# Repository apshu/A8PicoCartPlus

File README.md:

# A8PicoCart+ (A8PicoCart with autoboot and OLED GFX)

The aim of the A8PicoCart+ is to add autoboot feature to the excellent A8PicoCart. 

The autoboot eliminates the need to navigate trough a complex filesystem or many files (e.g. when playing zaxxon :). On power up it checks if the onboard I²C EERAM stores a valid filename. If the filename is valid, it loads the file automatically before showing the selector interface. If the last file can't be loaded (e.g. deleted) the selector GUI is shown.

If the selector UI is needed, press the Choose button on the cart during powerup.

A simple I²C OLED display is included for fun. The 128×64 monochrome display shows the loaded cart logo if the cartridge is recognized as extended format.

A new PCB was needed for the + functionality. The new PCB is 100% compatible with the original firmware, while utilizing the originally unconnected GP28 & GP29 pins for I²C.

3D printable box with the + features is available.

# A8PicoCart (UnoCart on a Raspberry Pi Pico clone)

The A8PicoCart is a multi-cart for the Atari 8-bit (XL/XE) which you can make at home with only basic soldering skills.
It is based on my earlier UnoCart design but uses a very inexpensive Raspberry Pi Pico clone (£2-3) for an easy build.

When plugged into a PC by USB it becomes a Mass Storage device allowing ROM/CAR/XEX & ATR files to be copied to the cartridge.
When plugged into an Atari these files are shown on the menu and the device will either emulate the selected cartridge type or
act as a XEX file launcher. It also has (very) limited support for ATR files allowing you to do some programming and save your
work to an ATR file.

This page contains everything you need to build the project - firmware to flash to your purple Pico clone, Kicad PCB design files to make a PCB and 3d print files for a nice case. The source code for everything is also here. There is also a manual detailing the full capabilities of the cartridge.

If you build an A8PicoCart consider donating to help fund this and my future projects:

## Quick Start

Get yourself a purple Raspberry Pi Pico clone (see [this thread](https://forums.raspberrypi.com/viewtopic.php?t=337976) for details) and order a PCB using the KiCad board files provided. You have a choice of two PCB designs - the XE design is for use uncased, with the Pico on the top surface. The XL/XE version is desgined to be mounted in a case (though can be used uncased too) with the Pico on the bottom/back surface. Once you have the Pico clone and PCB, solder the pico as pictured below, depending on your PCB version. Program the firmware onto the device by pressing BOOTSEL on the board and connecting to USB on a PC and drag the firmware (UF2 file) onto the device. It should then remount as A8-PICOCART so you can copy Atari CAR & XEX files to it. Unmount, then plug into your Atari and play! Optionally solder a reset button to reset back to the menu.

**Note**: this project does not work with the official green RPi Pico board. Although the official board has the same
number of physical pins (and will therefore fit in the PCB) - the actual pin functions are different and attempting to use
it may damage the Pico and/or your Atari. The purple clones are cheaper and have a greater number of usuable GPIO pins - 
this is required for the cartridge port emulation to work.

**Warning**: always disconnect from PC/USB before plugging into your Atari or you will damage your Atari and/or PC. This warning mainly
applies to the XE/uncased version of the PCB. The newest version of the XL/XE board makes it physically impossible to connect USB when the
cartridge is inserted in an Atari.

## Inserting the cartridge

Depending on which PCB you choose the Pico clone may be mounted on the front or back of the PCB. When you insert
the cartridge in the Atari make sure the "S..A" side of the cartridge edge (NOT the "1..15" side) is facing upwards (XE) or towards you (XL).

## Purple Pico clones

The firmware is designed for the Purple Pico clones with USB C connector and 16Megs of flash and a single button (BOOTSEL).
I've received these devices with two different types of SPI flash chips - Winbond and (slower) Z-bit. The firmware has been tested with both types.

The project defines a custom board with a higher value for PICO_FLASH_SPI_CLKDIV so it supports the slower Z-bit flash.

Be aware that it's possible you might get one with another type of flash memory chip that has not been tested.

## Reset button

You can solder a push button to the cartridge to get back to the menu and avoid wear on your Atari power switch.
When you reset the cartridge the Atari will crash - just push reset on the Atari itself to get back to the menu.

The button used is a 6x6mm thru-hole tactile momentary switch. If you are going to print a case, then 9mm+ height is suitable.
When you solder the button to the PCB - make sure the lower two holes in the PCB are bridged only when the button is pressed.

It works simply by pulling the RUN pin on the pico clone to ground to reset.

## 3D print files

The STL files can be used to print a 3 part (front, back and logo) cartridge shell. The 2-tone logo is achieved by
changing the filament at the correct z-position when printing a8pico_logo.stl. You'll also need two M3 15mm screws.

## Changelog

* 7 Oct 2023 - Add new PCB & case design files to make it impossible to insert USB when plugged into Atari. Add support for Microcart (CAR type 52) cartridges. Updated manual.
* 29 Oct 2023 - Adds 3 new cartridge types (thanks to ascrnet)

## Credits

* Design, hardware and firmware by Robin Edwards (electrotrains at atariage)
* XEX loader and OS modifications by Jonathan Halliday (flashjazzcat at atariage)
* Altirra LLE OS used with permision from Avery Lee (phaeron at atariage)

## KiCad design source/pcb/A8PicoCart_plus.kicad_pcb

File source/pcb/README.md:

# XL/XE version PCB (which fits the 3d printed case design)

* KiCad Project wirh 3D models 
* KiCad Version: 8.0.3, release build
* A zip file of the gerbers (JLCPCB specification).
* Updated version with EERAM and OLED display 
 
## PCB specifications:
* 70.04 × 53.8 mm
* 2 layers
* 1.6 mm thickness
* Minimum drill 0.3 mm
* Hard gold fingers with bevelled edge will make your PCB last longer, but at a much higher cost.

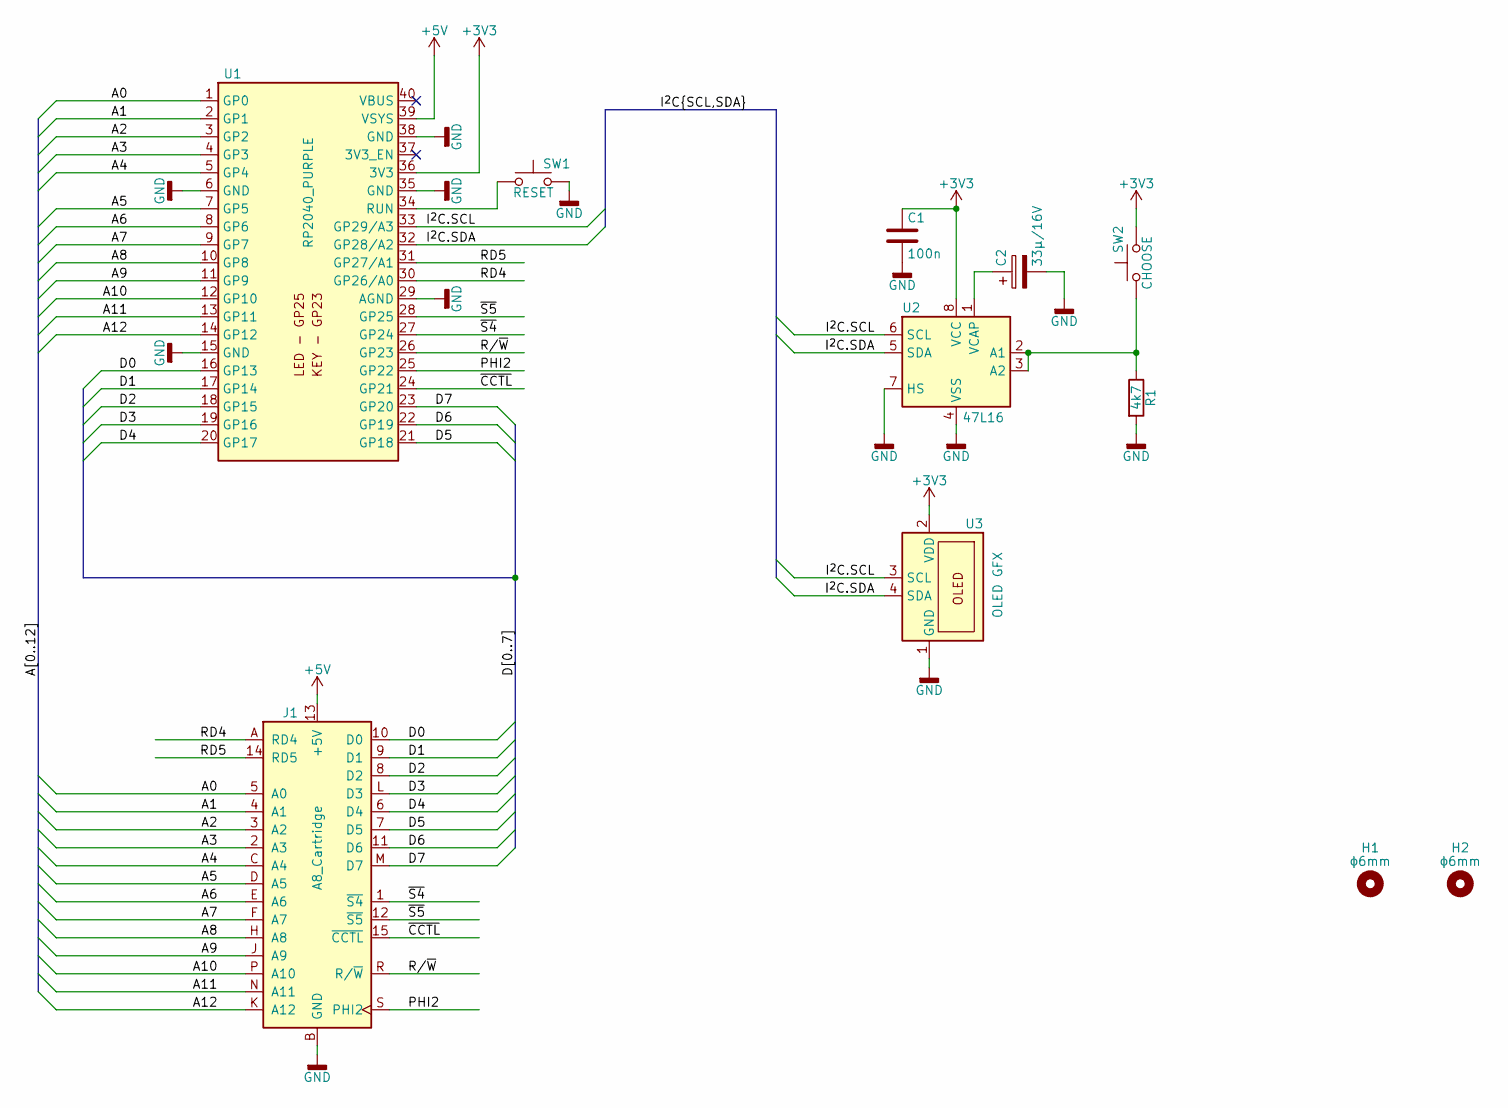
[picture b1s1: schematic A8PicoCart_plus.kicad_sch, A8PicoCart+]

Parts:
C1: 100n; C_0805_2012Metric_Pad1.18x1.45mm_HandSolder
C2: 33µ/16V; CP_Radial_D4.0mm_P2.00mm
H1, H2: ϕ6mm; MountingHole_6mm
J1: A8_Cartridge; Cartridge_A8
R1: 4k7; R_0805_2012Metric_Pad1.20x1.40mm_HandSolder
SW1: RESET; SW_PUSH_6mm_H8mm
SW2: CHOOSE; SW_PUSH_6mm_H8mm
U1: RP2040_PURPLE; RP2040_purple_nodbg
U2: 47L16; SOIC-8_3.9x4.9mm_P1.27mm
U3: OLED GFX; JST_XH_B4B-XH-A_1x04_P2.50mm_Vertical

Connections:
+3V3: C1.1, SW2.2, U1.36 (3V3), U2.8 (VCC), U3.2 (VDD)
+5V: J1.13 (+5V), U1.39 (VSYS)
/A0: J1.5 (A0), U1.1 (GP0)
/A1: J1.4 (A1), U1.2 (GP1)
/A2: J1.3 (A2), U1.3 (GP2)
/A3: J1.2 (A3), U1.4 (GP3)
/A4: J1.C (A4), U1.5 (GP4)
/A5: J1.D (A5), U1.7 (GP5)
/A6: J1.E (A6), U1.8 (GP6)
/A7: J1.F (A7), U1.9 (GP7)
/A8: J1.H (A8), U1.10 (GP8)
/A9: J1.J (A9), U1.11 (GP9)
/A10: J1.P (A10), U1.12 (GP10)
/A11: J1.N (A11), U1.13 (GP11)
/A12: J1.K (A12), U1.14 (GP12)
/D0: J1.10 (D0), U1.16 (GP13)
/D1: J1.9 (D1), U1.17 (GP14)
/D2: J1.8 (D2), U1.18 (GP15)
/D3: J1.L (D3), U1.19 (GP16)
/D4: J1.6 (D4), U1.20 (GP17)
/D5: J1.7 (D5), U1.21 (GP18)
/D6: J1.11 (D6), U1.22 (GP19)
/D7: J1.M (D7), U1.23 (GP20)
/I^{2}C.SCL: U1.33 (GP29/A3), U2.6 (SCL), U3.3 (SCL)
/I^{2}C.SDA: U1.32 (GP28/A2), U2.5 (SDA), U3.4 (SDA)
/PHI2: J1.S (PHI2), U1.25 (GP22)
/RD4: J1.A (RD4), U1.30 (GP26/A0)
/RD5: J1.14 (RD5), U1.31 (GP27/A1)
/R/~W: J1.R (R/~W), U1.26 (GP23)
/~CCTL: J1.15 (~CCTL), U1.24 (GP21)
/~S4: J1.1 (~S4), U1.27 (GP24)
/~S5: J1.12 (~S5), U1.28 (GP25)
GND: C1.2, C2.2, J1.B (GND), R1.2, SW1.2, U1.6 (GND), U1.15 (GND), U1.29 (AGND), U1.35 (GND), U1.38 (GND), U2.4 (VSS), U2.7 (HS), U3.1 (GND)
unnamed: SW1.1, U1.34 (RUN)
unnamed: R1.1, SW2.1, U2.2 (A1), U2.3 (A2)
unnamed: C2.1, U2.1 (VCAP)

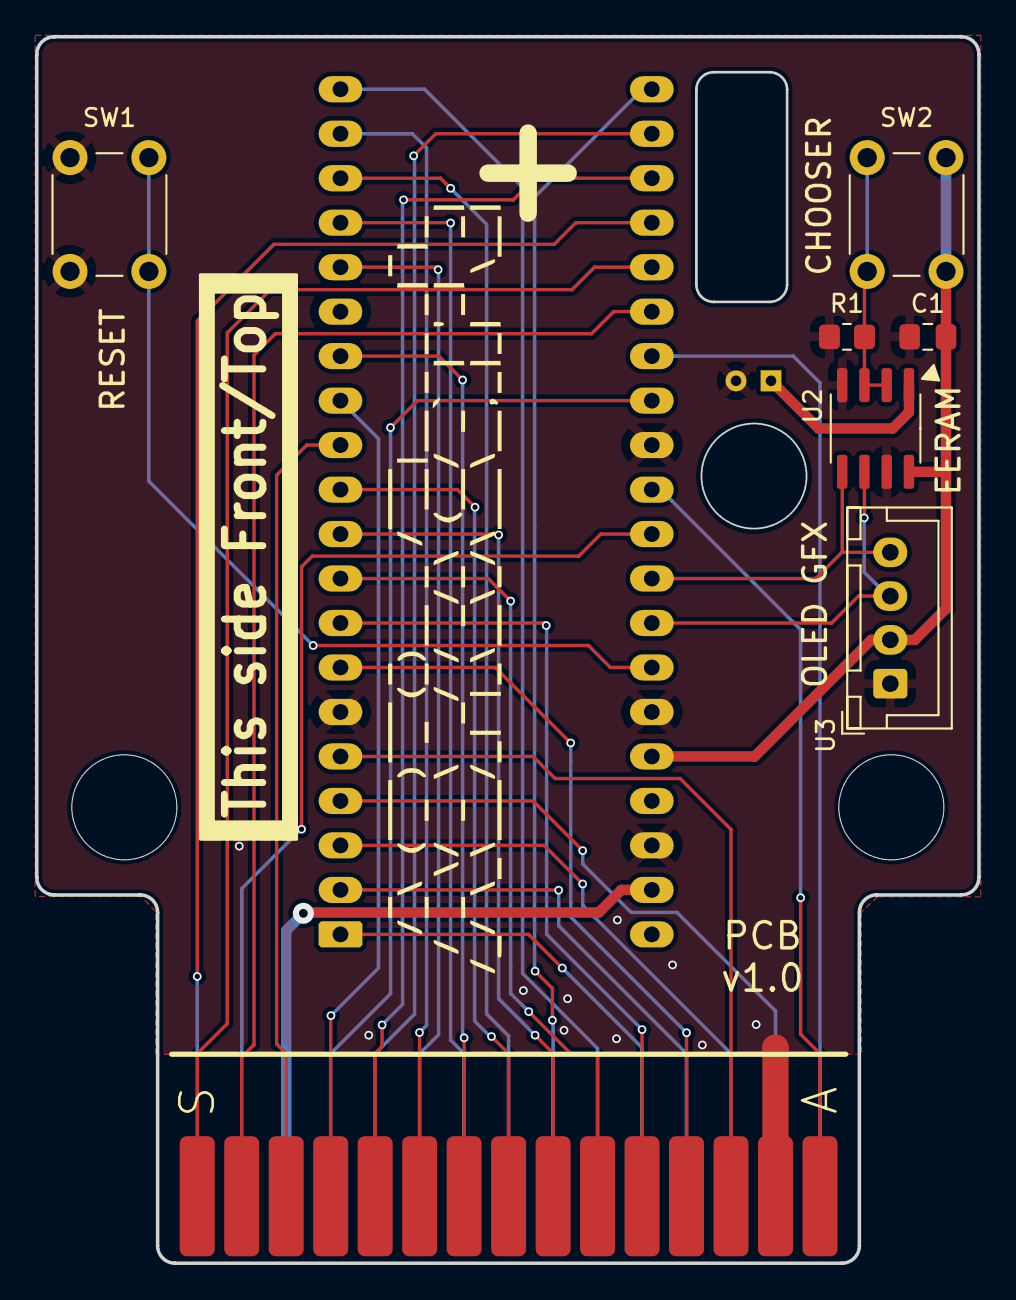
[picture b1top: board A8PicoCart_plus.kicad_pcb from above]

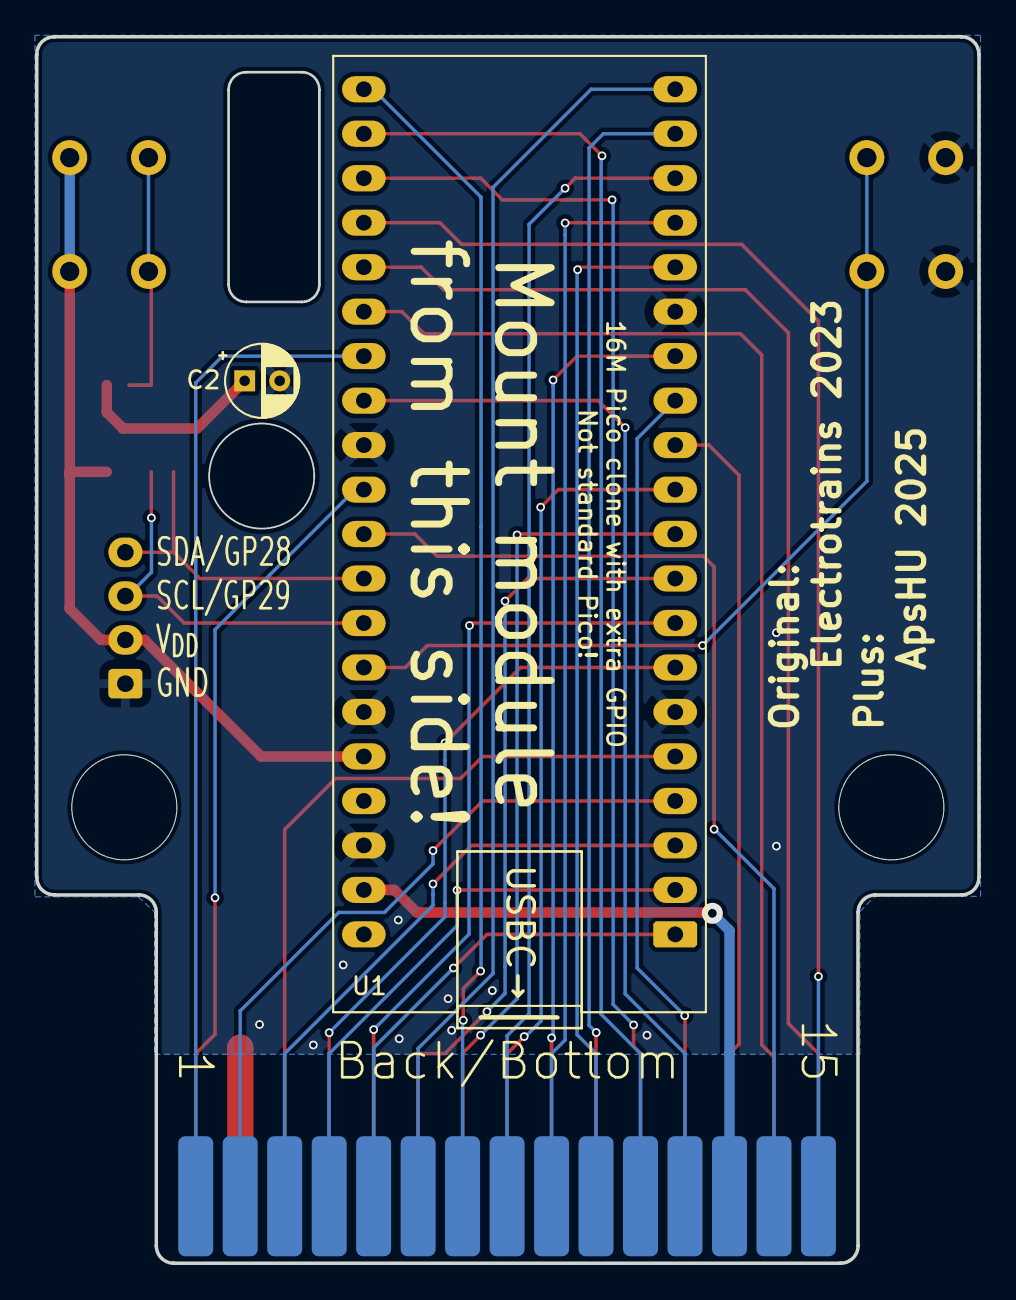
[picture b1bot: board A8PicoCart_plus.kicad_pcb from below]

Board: 2 copper layers, 53.8 x 70.0 mm, 11 parts (3 on the bottom side), 36 nets.

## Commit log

2024-06-30 Update atari_cart.c
    special case for williams 64K cartridges that are marked 32K
2024-07-31 Update A8PicoCart.asm
    Added support for TK-II for the start and end keys. The same is also included for normal keyboards.
    Comments and change of year are ordered
2024-09-06 TKII Support
    TKII support by user manterola from Atariage
2024-10-04 Joy 2B+ support and fix loader xex
2024-12-24 + statement
2024-12-24 Solves #3
2024-12-24 PicoSDK bumped to 2.1.0
2024-12-24 Pi Pico VS Code Extension add to CMAKE
2024-12-24 Add HOST mode I²C
2024-12-24 PHI2 pin configuration consistency
2024-12-24 I2C import sanity check
2024-12-24 I2C pins are not reconfigured as GPIO
2024-12-24 I2C initalization
2024-12-24 VS_code settings
2024-12-24 Add SSD1309 I²C driver Fixes apshu/A8PicoCartPlus#5
2024-12-24 Including SSD1306 I²C driver to CMakeLists
2024-12-24 Init OLED before USB enabled
2024-12-25 Refactored driver API
2024-12-25 GFX routines are non-static now
2024-12-25 Driver routines in .h
2024-12-25 Ignore VSCode
2024-12-25 More common constants moved to header
2024-12-25 Changed board type to the actual board on PCB
2024-12-25 Due to Pico type change, memory size redefinition not required
2024-12-25 Default I²C pins reconfigured for the project Fixes apshu/A8PicoCartPlus#13
2024-12-25 Show welcome message on the display during USB operation Closes apshu/A8PicoCartPlus#8
2024-12-25 new FW ID and year Fixes apshu/A8PicoCartPlus#16
2024-12-28 Old PCB files are not needed, A8PicoCartPlus PCB is 100% compatible with the old FW
2024-12-28 A8 PicoCart+ PCB, schematics,3D models and manufacturing files Closes apshu/A8PicoCartPlus#9
2025-01-02 Add helper for VSCODE Fixes apshu/A8PicoCartPlus#20
2025-01-02 Add readme instructions for VSCode
2025-01-02 menu text modified Fixes apshu/A8PicoCartPlus#19
2025-01-02 Binary file changed and rom.h modified in the PICO code Closes apshu/A8PicoCartPlus#19
2025-01-04 Add 47L16 EERAM driver Closes apshu/A8PicoCartPlus#6
2025-01-04 EERAM chip_addr constant names under EERAMI2C namespace Fixes apshu/A8PicoCartPlus#6
2025-01-04 Anonymous label for skipping the reset FLASH routine
2025-01-04 Autoboot ASM
2025-01-05 Better comments
2025-01-05 Rom code with "skip AB" on pico
2025-01-05 EERAM memory layout defined
2025-01-05 CART_CMD_GET_AUTOBOOT_INFO reads and verifies EERAM data
2025-01-05 Add EERAMI2C_verifiedWriteBuffer for verified writes
2025-01-05 Atari BPT to debug autoboot
2025-01-05 reset_eeram added
2025-01-05 EERAM is reset when filesystem is reset
2025-01-05 EERAM boot only if no fs based autoboot
2025-01-05 Revert "EERAM boot only if no fs based autoboot"
    This reverts commit 280ecc6d0caf5f8ac136993d2f14786536b5573b.
2025-01-05 get_filename function
2025-01-05 Fix get_filename
2025-01-05 Length barrier on string copy
2025-01-05 fs_based autoboot from "AUTOBOOT" file. Empty file skips autoboot process
2025-01-05 Basic sanity check on autoboot request
2025-01-05 Improved error message
2025-01-06 Skip FS and EERAM based autoboot if NOAUTOBOOT button pressed
2025-01-06 eeramDataBuf now global variable
2025-01-06 Storing last executed file info to EERAM
2025-01-18 Added vsocde settings to gitignore
2025-01-18 Gitignore editor settings
2025-01-18 Improved comment
2025-01-18 Optional OLED window and menu button
2025-01-18 Included cart-tool Git module
2025-01-18 Adjusted positions and removed frame from +logo
2025-01-18 Eliminate old versions
2025-01-18 Eliminate debug message
2025-01-18 Constants from common file, no logo only
2025-01-18 Improved comments
2025-01-18 OLED, menu and more constants to common include
2025-01-18 Makefile adjusted to changes
2025-01-18 Remove old files
2025-01-18 Renamed generator files, removed generatums
2025-01-18 Moved 3D shell generator sources to source folder
2025-01-18 Shell for 3D printing Closes A8PicoCartPlus OLED modified casing apshu/A8PicoCartPlus#10
2025-01-18 PCB separated to release and sources
2025-01-30 Update a8picoplus_front.scad
    Window for OLED made bigger
2025-01-30 Case OLED cutout 25.6x17.6mm Fixes apshu/A8PicoCartPlus#34
2025-01-30 Move firmware to release Closes apshu/A8PicoCartPlus#31
2025-02-03 Removed double allocated OLED frame buffer Fixes apshu/A8PicoCartPlus#8
2025-02-03 Skeleton for external artwork file loader
2025-02-03 LCD format loader and display framebuffer
2025-03-01 Autoboot
2025-03-01 Shows .LCD images on OLED with working autoboot
2025-03-01 Erase LCD screen on reset Fixes apshu/A8PicoCartPlus#38
